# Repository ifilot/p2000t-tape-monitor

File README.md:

# P2000T Tape Monitor

## Features

This project is still under development. Below a list of features can be found.
Checked features are implemented, unchecked features are work in progress.

- [x] Launch tape files from data cartridge in SLOT2
- [x] Write tape data to data cartridge in SLOT2
- [ ] Write data back to tapes from the data cartridge

## Explainer

In the image below, the working of the data cartridge is schematically shown.
In the conventional approach, the user would start the P2000T and load programs
from the cassette. Under the hood, data is copied from the cassette to the
internal memory after which the program can be started.

The data cartridge essentially imitates this process. Upon boot, a driver is 
loaded from the data cartridge into memory and launched. This driver
scans the external ROM chip for programs and shows a list of those programs. The
user can then select a program and executes it. Upon selection, the program is
first copied from the external chip to the internal RAM chip in the data cartridge.
Next, the driver is unloaded from memory, and the new data is copied from the 
RAM chip to the same position as where normally cassette data is copied. 
Finally, the `RUN` command is executed which starts the program.

## Contents
This repository is organized as follows

* `basicmod`: Modified BASIC ROM. This ROM is needed for the cartridge in SLOT1.
* `cassette-utility`: Source code of the SLOT1 program to copy programs and data
  from the data cassette to the data cartridge.
* `docs`: Technical documentation; mainly needed for development.
* `flasher`: SLOT1 program to transfer the launcher from external ROM chip
  on the data cartridge to the internal ROM.
* `gui`: GUI to add and delete programs from the data cartridge and to format a
  chip.
* `launcher`: Source code of the launcher application.
* `pcb`: PCBs for the SLOT2 data cartridge. Also includes .stl files for the cartridge enclosure.

## Files

The latest version of the files below can be obtained from the action artifacts
of the [last build](https://github.com/ifilot/p2000t-tape-monitor/actions/workflows/build.yml).

* [`BASICBOOTSTRAP.BIN`](https://github.com/ifilot/p2000t-tape-monitor/releases/latest/download/BASICBOOTSTRAP.BIN): 
  Modified BASIC cartridge. This is a SLOT1 cartridge.
* [`CASSETTE_UTILITY.BIN`](https://github.com/ifilot/p2000t-tape-monitor/releases/latest/download/CASSETTE_UTILITY.BIN): 
  Utility for copying files directly from the cassette to the (external) ROM chip. This is a SLOT1 cartridge.
* [`FLASHER.BIN`](https://github.com/ifilot/p2000t-tape-monitor/releases/latest/download/FLASHER.BIN):
  Flasher for the data cartridge driver. This is a SLOT1 cartridge that copies 
  the driver from the external to the internal ROM on the SLOT2 cartridge.
* [`LAUNCHER.BIN`](https://github.com/ifilot/p2000t-tape-monitor/releases/latest/download/LAUNCHER.BIN): 
  Driver for the data cartridge. This driver is stored on the internal ROM of 
  the SLOT2 cartridge.
* [`p2000t-fat-flasher-installer-win64.exe`](https://github.com/ifilot/p2000t-tape-monitor/releases/latest/download/p2000t-fat-flasher-installer-win64.exe): 
  Windows installer for the Flasher GUI. This GUI is used to put cassette files 
  on a ROM chip which can be loaded on the P2000T.

## File system

Data is stored on the ROM using a custom file system. Specifications of the file
system are documented [in a separate file](docs/fat.md).

## FAQ

* Where can I find programs?

  *A rather huge archive of P2000T cassette programs 
  (which is also being actively maintained), can be found in the
  [P2000T Preservation Project](https://github.com/p2000t/software) repository.*
* Where can I find the documentation?

  *All documentation can be found on the [philips-p2000t.nl](https://philips-p2000t.nl) website.*

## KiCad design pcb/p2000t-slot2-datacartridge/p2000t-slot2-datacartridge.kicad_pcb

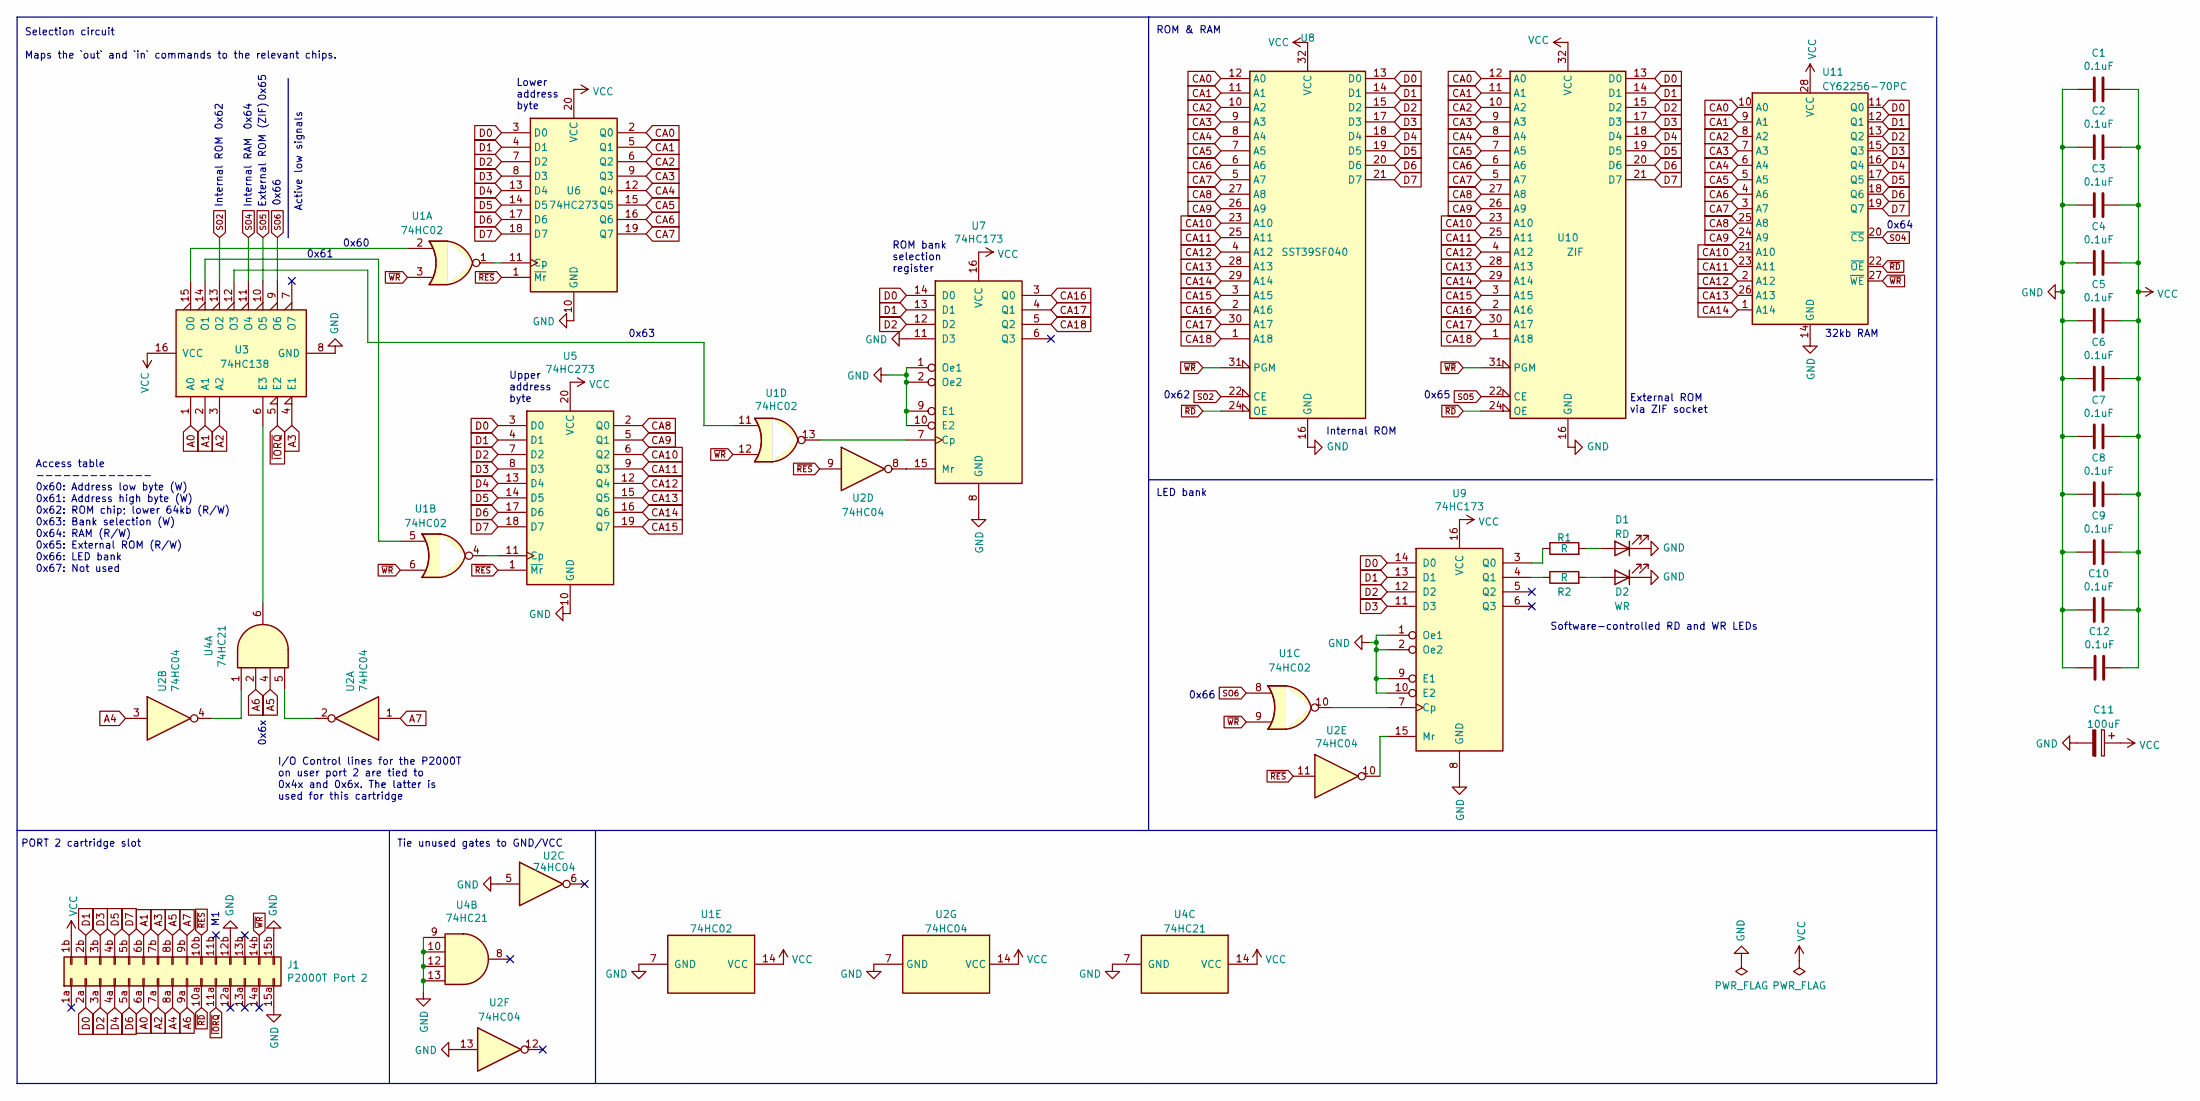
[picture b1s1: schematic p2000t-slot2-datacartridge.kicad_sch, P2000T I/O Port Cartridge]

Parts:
C1, C2, C3, C4, C5, C6, C7, C8, C9, C10, C12: 0.1uF; C_Disc_D5.0mm_W2.5mm_P5.00mm
C11: 100uF; CP_Radial_D6.3mm_P2.50mm
D1: RD; LED_D5.0mm
D2: WR; LED_D5.0mm
J1: P2000T Port 2; p2000t_cartridge_edge
R1, R2: R; R_Axial_DIN0207_L6.3mm_D2.5mm_P7.62mm_Horizontal
U1: 74HC02; DIP-14_W7.62mm_Socket
U2: 74HC04; DIP-14_W7.62mm_Socket
U3: 74HC138; DIP-16_W7.62mm_Socket
U4: 74HC21; DIP-14_W7.62mm_Socket
U5, U6: 74HC273; DIP-20_W7.62mm_Socket
U7, U9: 74HC173; DIP-16_W7.62mm_Socket
U8: SST39SF040; PLCC-32_THT-Socket
U10: ZIF; DIP_Socket-32_W11.9_W12.7_W15.24_W17.78_W18.5_3M_232-1285-0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
U11: CY62256-70PC; DIP-28_W15.24mm_Socket

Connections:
A0: J1.6a, U3.1 (A0)
A1: J1.6b, U3.2 (A1)
A2: J1.7a, U3.3 (A2)
A3: J1.7b, U3.4 (E1)
A4: J1.8a, U2.3
A5: J1.8b, U4.4
A6: J1.9a, U4.2
A7: J1.9b, U2.1
CA0: U6.2 (Q0), U8.12 (A0), U10.12 (A0), U11.10 (A0)
CA1: U6.5 (Q1), U8.11 (A1), U10.11 (A1), U11.9 (A1)
CA2: U6.6 (Q2), U8.10 (A2), U10.10 (A2), U11.8 (A2)
CA3: U6.9 (Q3), U8.9 (A3), U10.9 (A3), U11.7 (A3)
CA4: U6.12 (Q4), U8.8 (A4), U10.8 (A4), U11.6 (A4)
CA5: U6.15 (Q5), U8.7 (A5), U10.7 (A5), U11.5 (A5)
CA6: U6.16 (Q6), U8.6 (A6), U10.6 (A6), U11.4 (A6)
CA7: U6.19 (Q7), U8.5 (A7), U10.5 (A7), U11.3 (A7)
CA8: U5.2 (Q0), U8.27 (A8), U10.27 (A8), U11.25 (A8)
CA9: U5.5 (Q1), U8.26 (A9), U10.26 (A9), U11.24 (A9)
CA10: U5.6 (Q2), U8.23 (A10), U10.23 (A10), U11.21 (A10)
CA11: U5.9 (Q3), U8.25 (A11), U10.25 (A11), U11.23 (A11)
CA12: U5.12 (Q4), U8.4 (A12), U10.4 (A12), U11.2 (A12)
CA13: U5.15 (Q5), U8.28 (A13), U10.28 (A13), U11.26 (A13)
CA14: U5.16 (Q6), U8.29 (A14), U10.29 (A14), U11.1 (A14)
CA15: U5.19 (Q7), U8.3 (A15), U10.3 (A15)
CA16: U7.3 (Q0), U8.2 (A16), U10.2 (A16)
CA17: U7.4 (Q1), U8.30 (A17), U10.30 (A17)
CA18: U7.5 (Q2), U8.1 (A18), U10.1 (A18)
D0: J1.2a, U5.3 (D0), U6.3 (D0), U7.14 (D0), U8.13 (D0), U9.14 (D0), U10.13 (D0), U11.11 (Q0)
D1: J1.2b, U5.4 (D1), U6.4 (D1), U7.13 (D1), U8.14 (D1), U9.13 (D1), U10.14 (D1), U11.12 (Q1)
D2: J1.3a, U5.7 (D2), U6.7 (D2), U7.12 (D2), U8.15 (D2), U9.12 (D2), U10.15 (D2), U11.13 (Q2)
D3: J1.3b, U5.8 (D3), U6.8 (D3), U8.17 (D3), U9.11 (D3), U10.17 (D3), U11.15 (Q3)
D4: J1.4a, U5.13 (D4), U6.13 (D4), U8.18 (D4), U10.18 (D4), U11.16 (Q4)
D5: J1.4b, U5.14 (D5), U6.14 (D5), U8.19 (D5), U10.19 (D5), U11.17 (Q5)
D6: J1.5a, U5.17 (D6), U6.17 (D6), U8.20 (D6), U10.20 (D6), U11.18 (Q6)
D7: J1.5b, U5.18 (D7), U6.18 (D7), U8.21 (D7), U10.21 (D7), U11.19 (Q7)
GND: C1.2, C2.2, C3.2, C4.2, C5.2, C6.2, C7.2, C8.2, C9.2, C10.2, C11.2, C12.2, D1.1 (K), D2.1 (K), J1.12b, J1.15a, J1.15b, U1.7 (GND), U2.5, U2.7 (GND), U2.13, U3.8 (GND), U4.7 (GND), U4.9, U4.10, U4.12, U4.13, U5.10 (GND), U6.10 (GND), U7.1 (Oe1), U7.2 (Oe2), U7.8 (GND), U7.9 (E1), U7.10 (E2), U7.11 (D3), U8.16 (GND), U9.1 (Oe1), U9.2 (Oe2), U9.8 (GND), U9.9 (E1), U9.10 (E2), U10.16 (GND), U11.14 (GND)
unnamed: D1.2 (A), R1.2
unnamed: D2.2 (A), R2.2
unnamed: U2.2, U4.5
unnamed: U2.4, U4.1
unnamed: U3.6 (E3), U4.6
unnamed: U1.2, U3.15 (O0)
unnamed: U1.5, U3.14 (O1)
unnamed: U1.11, U3.12 (O3)
unnamed: U1.4, U5.11 (Cp)
unnamed: U1.1, U6.11 (Cp)
unnamed: U1.13, U7.7 (Cp)
unnamed: U2.8, U7.15 (Mr)
unnamed: U1.10, U9.7 (Cp)
unnamed: U2.10, U9.15 (Mr)
unnamed: R1.1, U9.3 (Q0)
unnamed: R2.1, U9.4 (Q1)
SO2: U3.13 (O2), U8.22 (CE)
SO4: U3.11 (O4), U11.20 (~CS)
SO5: U3.10 (O5), U10.22 (CE)
SO6: U1.8, U3.9 (O6)
VCC: C1.1, C2.1, C3.1, C4.1, C5.1, C6.1, C7.1, C8.1, C9.1, C10.1, C11.1, C12.1, J1.1b, U1.14 (VCC), U2.14 (VCC), U3.16 (VCC), U4.14 (VCC), U5.20 (VCC), U6.20 (VCC), U7.16 (VCC), U8.32 (VCC), U9.16 (VCC), U10.32 (VCC), U11.28 (VCC)
~IORQ: J1.11a, U3.5 (E2)
~RD: J1.10a, U8.24 (OE), U10.24 (OE), U11.22 (~OE)
~RES: J1.10b, U2.9, U2.11, U5.1 (~Mr), U6.1 (~Mr)
~WR: J1.14b, U1.3, U1.6, U1.9, U1.12, U8.31 (PGM), U10.31 (PGM), U11.27 (~WE)

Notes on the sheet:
Active low signals
32kb RAM
0x64
Access table ------------- 0x60: Address low byte (W) 0x61: Address high byte (W) 0x62: ROM chip; lower 64kb (R/W) 0x63: Bank selection (W) 0x64: RAM (R/W) 0x65: External ROM (R/W) 0x66: LED bank 0x67: Not used
Tie unused gates to GND/VCC
Internal ROM
PORT 2 cartridge slot
External ROM via ZIF socket
0x6x
Software-controlled RD and WR LEDs
ROM bank selection register
0x66
I/O Control lines for the P2000T on user port 2 are tied to 0x4x and 0x6x. The latter is used for this cartridge
0x60
ROM & RAM
Selection circuit Maps the `out` and `in` commands to the relevant chips.
0x65
Upper address byte
0x63
External ROM (ZIF)
0x62
0x61
Lower address byte
LED bank
Internal RAM

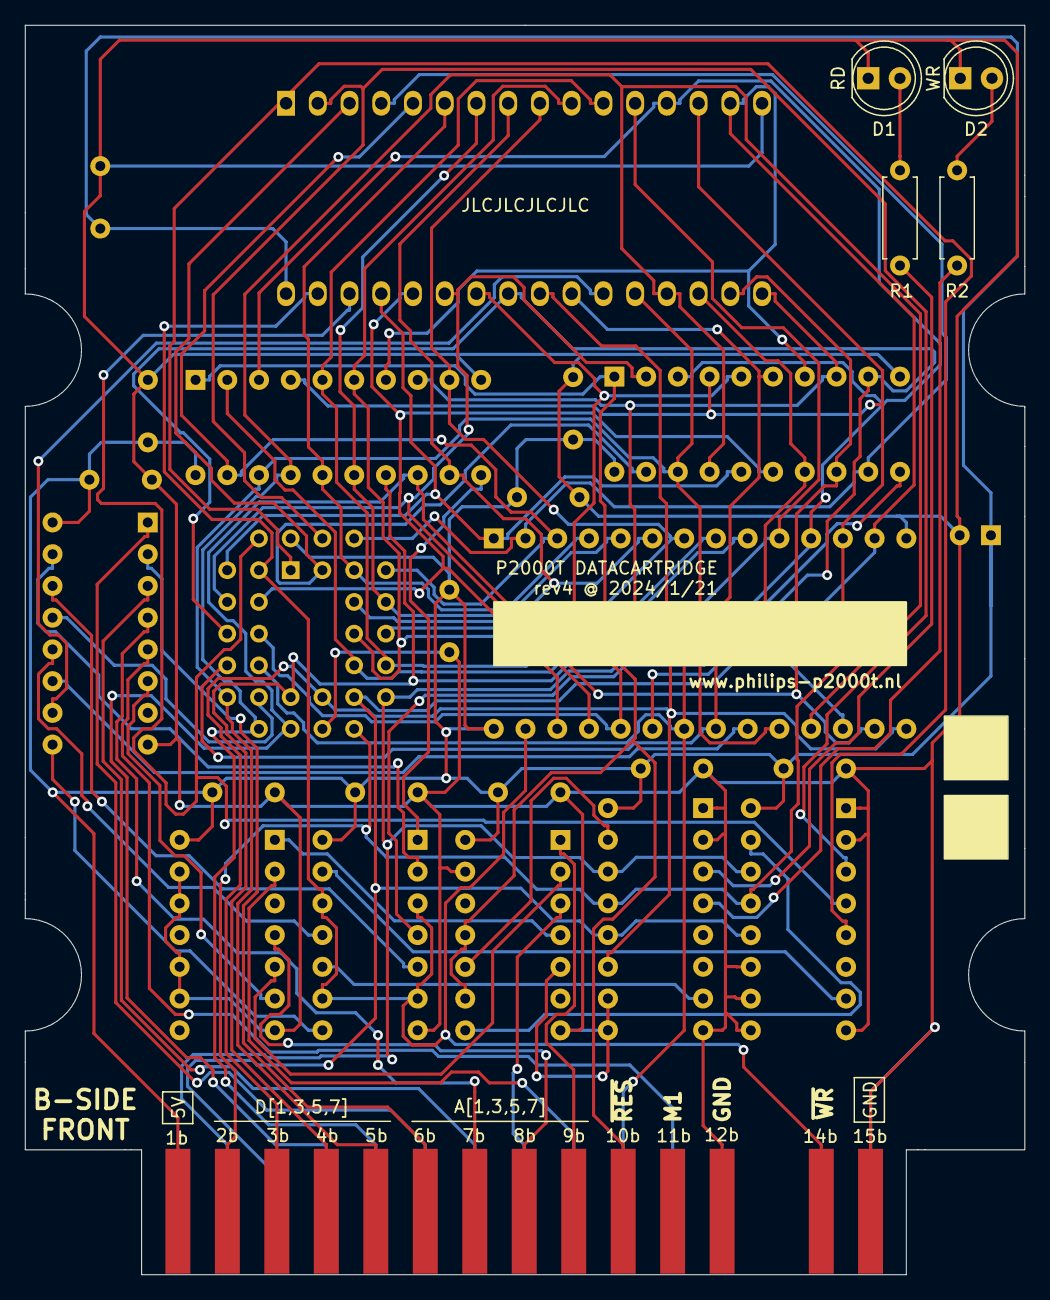
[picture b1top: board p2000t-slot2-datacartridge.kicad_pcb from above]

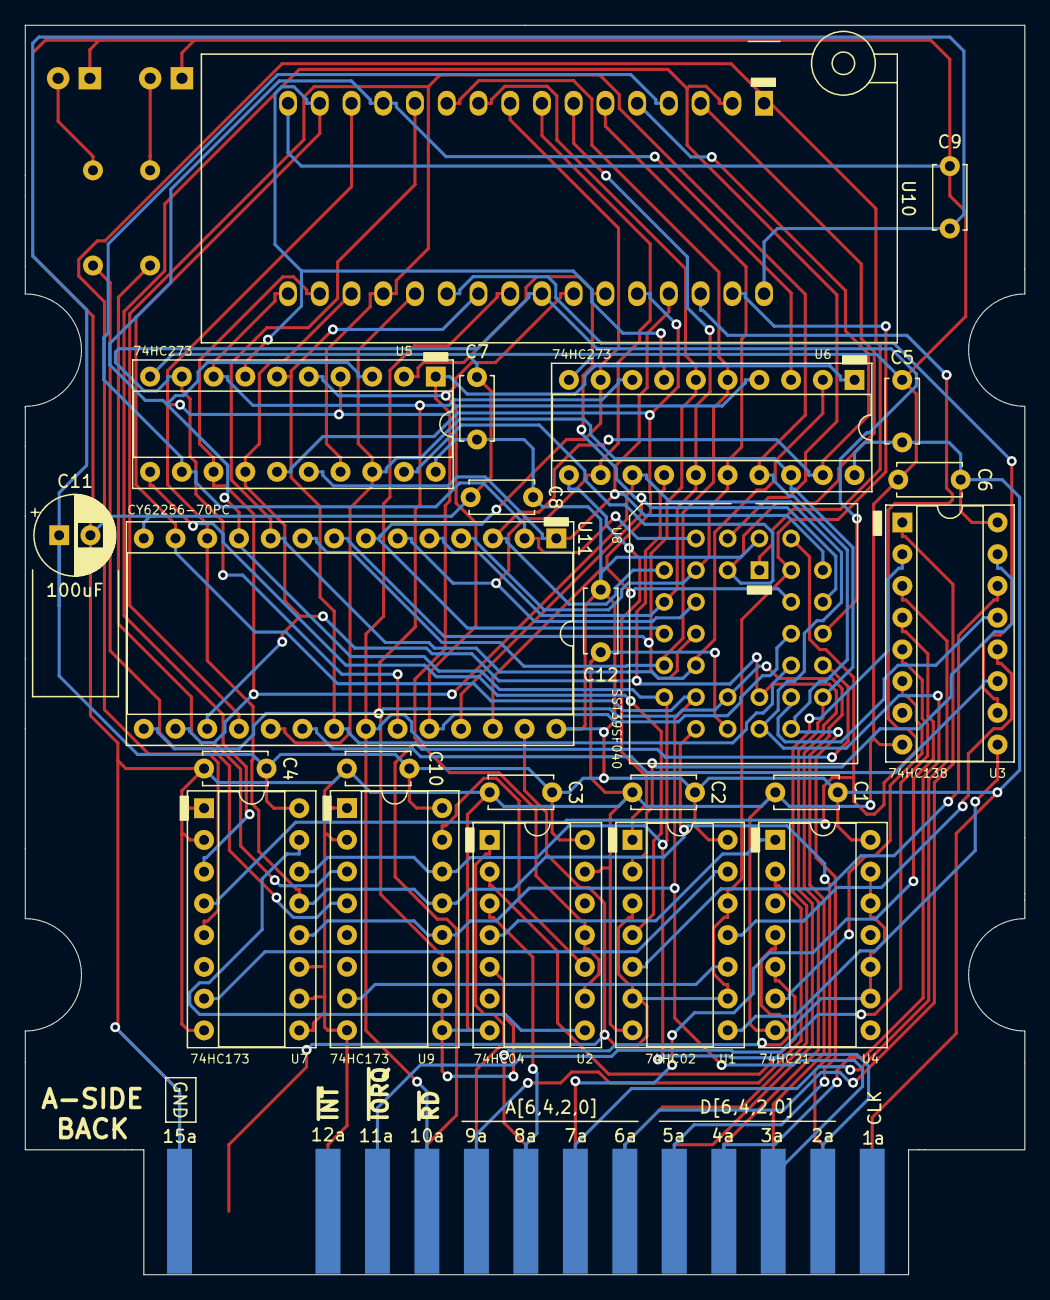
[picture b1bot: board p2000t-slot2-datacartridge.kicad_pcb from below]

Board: 2 copper layers, 80.0 x 100.0 mm, 28 parts (24 on the bottom side), 61 nets.

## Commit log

2023-08-08 Expanding documentation
2023-08-08 Adding CRC16 functions
2023-08-09 Implemented CRC-16 checksum
2023-08-09 Initial commit external RAM routines
2023-08-09 Fixing bug in stairtest
2023-08-10 Fixing bugs in RAM reading and in monitor code
2023-08-10 Adding routine to copy start blocks from rom to ram
2023-08-11 Storing filenames in external ram
2023-08-12 Adding program listing
2023-08-13 Completing file list viewer and changing register types for some utility functions
2023-08-14 Moving pointer
2023-08-17 Initial commit refactoring monitor routines
2023-08-17 Done refactoring monitor routine
2023-08-17 Initial commit file info
2023-08-17 Building linked list
2023-08-17 Initial commit file deletion
2023-08-18 Adding headers
2023-08-19 Attempt to format header
2023-08-20 Expanding on file deletion procedure
2023-08-20 Migrating register functions to memory
2023-08-21 Succesful wipe
2023-08-21 Removing log messages
2023-08-21 Initial commit overview ROM
2023-08-22 Fixing overview screen
2023-08-22 Showing file blocks and adding modal
2023-08-23 Adding slot2 PCB
2023-08-23 Cleaning up repo
2023-09-01 Initial commit launch-os
2023-09-02 Printing titles
2023-09-02 Initial commit GUI
2023-09-02 Reading files and putting data in hexviewer
2023-09-02 Initial commit location visualization
2023-09-03 Fixing block image
2023-09-03 Updating icon, adding progress bars, adding comments
2023-09-03 Adding CRC16 checksum
2023-09-03 Polishing checksums
2023-09-03 Adding saving file
2023-09-03 Adding emulator source
2023-09-09 Changing layer thickness and adding case
2023-09-09 Removing step file
2023-09-11 Improving case
2023-09-20 Adding quick deployment script
2023-09-20 Expanding launchos
2023-09-24 Refactoring source code
2023-09-24 Browsing through applications
2023-09-24 Refactoring coding style and creating program lists
2023-09-24 Outputting file list
2023-09-24 Accepting keybuffer input
2023-09-26 Improving launch os and creating copy (flash) utility
2023-09-28 Adding romhack script
2023-09-30 Polishing datacartridge flasher utility
2023-09-30 Attempting to connect launcher program to bootstrap routines
2023-09-30 Launching applications from BASIC environment
2023-10-01 Optimizing program
2023-10-01 Polishing software
2023-10-01 Initial commit CI/CD
2023-10-01 Expanding CI/CD
2023-10-01 Fixing typo
2023-10-01 Tuning compilation for CICD
2023-10-01 Adding firmware flasher to CI/CD
2023-10-01 Fixing uppercase issues
2023-10-01 Fixing names
2023-10-01 Interim commit adding cas files to FAT
2023-10-01 Adding files to ROM
2023-10-01 Tuning GUI
2023-10-05 Adding cases
2023-10-05 Clearing filetable upon identifying rom chip
2023-10-07 Adding synchronization routines
2023-10-07 Adding debug log and fixing metadata
2023-10-08 Adding sector read instructions
2023-10-08 Adding file deletion
2023-10-08 Fixing bug in pagination
2023-10-09 Adding sync blockmap, expanding README.md and adding GUI compilation to CI/CD
2023-10-09 Expanding README.md and fixing compilation gui
2023-10-09 Adding icon and installer
2023-10-09 Exapnding README
2023-10-09 Adding firmware, PCB schematics, documentation (#4)
    * Initial commit file info
    * Building linked list
    * Initial commit file deletion
    * Adding headers
    * Attempt to format header
    * Expanding on file deletion procedure
2023-10-11 Improving lay-out board
2023-10-11 Improving GUI
2023-10-11 Adding sudo
2023-10-11 Fixing path
2023-10-11 Adding checkout
2023-10-11 Adding serialport
2023-10-11 Expanding README.md
2023-10-11 Features (#5)
    * Improving GUI
    * Adding sudo
    * Fixing path
    * Adding checkout
    * Adding serialport
    * Expanding README.md
2023-10-12 Fixing incorrect layer in gerber files
2023-10-13 Adding chip formatting
2023-10-13 Implementing rom formatting and replacing icon
2023-10-13 Implementing rom formatting (#6)
    * Adding chip formatting
    * Implementing rom formatting and replacing icon
2023-10-13 Checking for ROM id, fixing bug in program numbers, expanding to 39sf010 and 39sf020 chips
2023-10-14 Adding version numbers and polishing launch-os
2023-10-14 Adding features (#7)
    * Adding chip formatting
    * Implementing rom formatting and replacing icon
    * Checking for ROM id, fixing bug in program numbers, expanding to 39sf010 and 39sf020 chips
    * Adding version numbers and polishing launch-os
    * Expanding CI/CD
2023-10-14 Changing names
2023-10-15 Adding code coverage and license
2023-10-15 Improving exception handling
2023-10-15 Fixing CMakeList.txt
2023-10-15 Set filesize of flasher to 16k and launcher-os to 8k
2023-10-15 Patch version 0.2.1 (#8)
    * Improving exception handling
    * Fixing CMakeList.txt
    * Set filesize of flasher to 16k and launcher-os to 8k
2023-10-15 Removing duplicate case files
2023-10-28 Initial commit rev2 and implementing LEDs in firmware flasher
2023-10-28 Fixing bug that triggered undefined behavior when writing to FAT chip
2023-10-29 Fixing incorrect RES line
2023-10-29 Building rev2 of the data cartridge
2023-10-29 Refactoring serial interface
2023-10-29 Adding leds to launcher
2023-10-29 Adding new emulator
2023-10-29 Expanding README
2023-10-29 Adding .dll files
2023-10-29 Adding missing files
2023-10-29 Fixing bugs, adding icons, adding explainers
2023-10-29 Patch 0.3.0 (#9)
    * Improving lay-out board
    * Fixing incorrect layer in gerber files
    * Initial commit rev2 and implementing LEDs in firmware flasher
    * Fixing bug that triggered undefined behavior when writing to FAT chip
    * Fixing incorrect RES line
    * Building rev2 of the data cartridge
2023-11-04 Initial commit cassette-utility
2023-11-04 Retrieving data from tape
2023-11-04 Implementing file progression
2023-11-04 Implementing copying files from cassette to chip
2023-11-04 Fixing reference in build.yml
2023-11-04 Polishing UI
2023-11-05 Making slight adjustment to launcher and bootstrap
2023-11-19 Tuning case
2023-11-22 Fix bug in deployment of BASIC ROM
2024-01-01 Uploading checksums
2024-01-01 Fixing ids
2024-01-01 Installing numpy
2024-01-01 Another attempt
2024-01-01 Improved Datacartridge PCB (#10)
    * Improving lay-out board
    * Fixing incorrect layer in gerber files
    * Initial commit rev2 and implementing LEDs in firmware flasher
    * Fixing incorrect RES line
    * Building rev2 of the data cartridge
2024-01-01 Removing main files
2024-01-01 Patching compilation instructions
2024-01-03 Patch 0.4.0 (#11)
    * Initial commit cassette-utility
    * Retrieving data from tape
    * Implementing file progression
    * Implementing copying files from cassette to chip
    * Fixing reference in build.yml
    * Polishing UI
2024-01-12 Initial commit revision
2024-01-12 Interim commit
2024-01-13 Rerouting
2024-01-19 Adding RAM validation
2024-01-19 Polishing lay-out and optimizing code
2024-01-19 Allow loading of programs at different deploy addresses, removing obsolete source code.
2024-01-21 Fixing bug in PCB
2024-02-04 Revision 3 and 4 of the PCB (#12)
    * Initial commit revision
    * Interim commit
    * Rerouting
    * Fixing bug in PCB
2024-02-04 Develop (#13)
    * Initial commit cassette-utility
    * Retrieving data from tape
    * Implementing file progression
    * Implementing copying files from cassette to chip
    * Fixing reference in build.yml
    * Polishing UI
2024-03-16 Refactoring source code and updating README.md
2024-03-16 Adjusting compilation folder
2024-03-16 Specify installation folder
2024-03-16 Incrementing version number
2024-03-16 Refactoring cassette utility
2024-03-16 Further tuning cassette utility
2024-03-16 Improving cassette utility (#14)
    * Refactoring source code and updating README.md
    * Adjusting compilation folder
    * Specify installation folder
    * Incrementing version number
    * Refactoring cassette utility
    * Further tuning cassette utility
2024-03-16 Updating README.md
2024-03-16 Fixing filenames
2024-03-17 Modifying build procedure
2024-03-17 Adding XOR a before RUN
2024-06-15 Applying text changes
2024-06-15 Applying text changes (#15)

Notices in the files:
README.md:
License: GPL v3
